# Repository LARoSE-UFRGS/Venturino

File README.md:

# Venturino: an Arduino-Based Open-Hardware platform for educational purposes

About this repo: Schematics, PCB layouts and Software libs.

*This project is intended to be arduino compatible.

LARoSE - UFRGS

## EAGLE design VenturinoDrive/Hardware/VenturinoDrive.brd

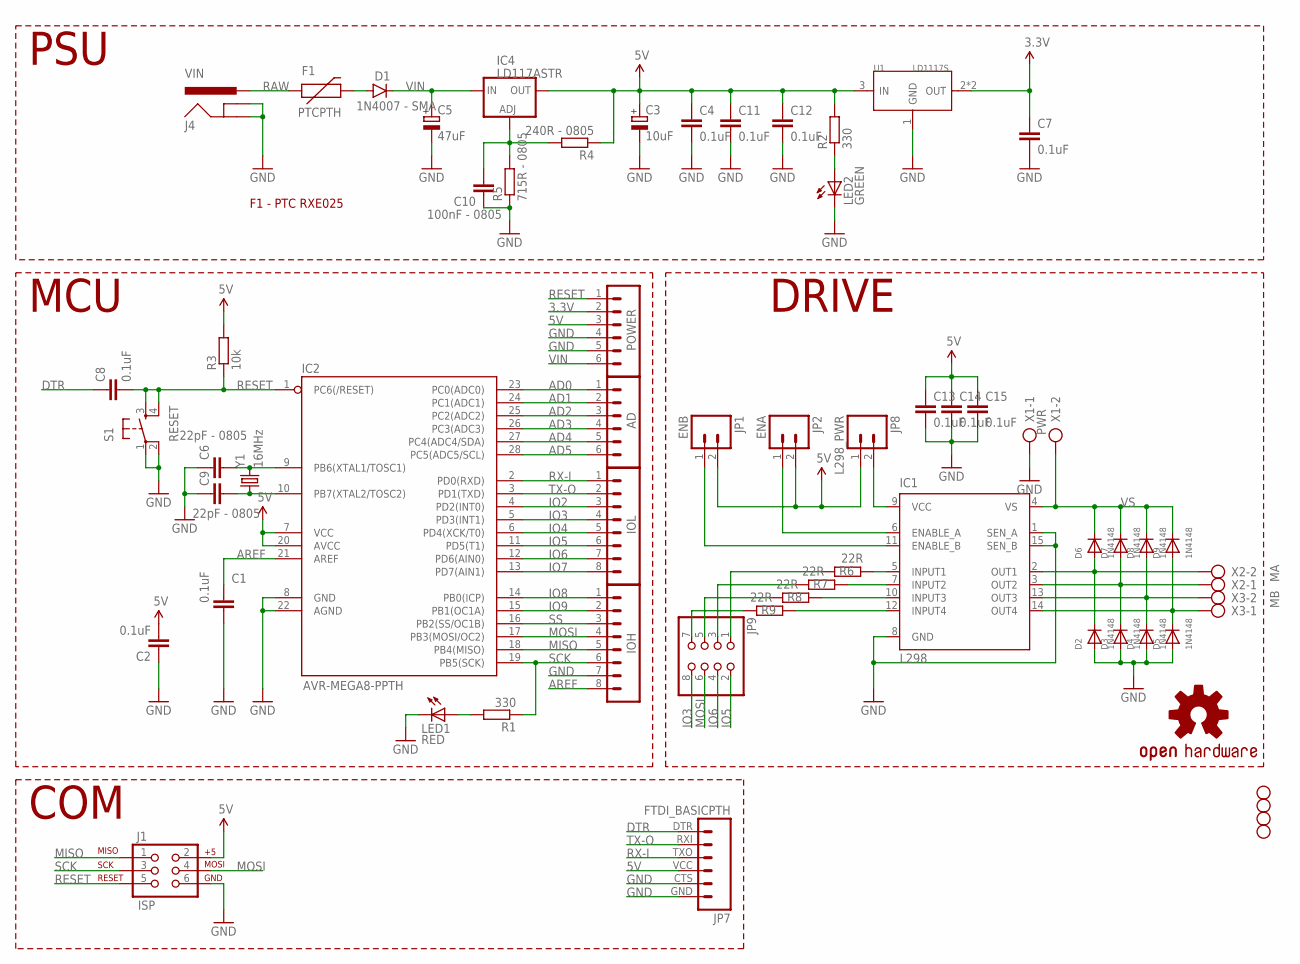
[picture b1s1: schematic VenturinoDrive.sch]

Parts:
AD: M06SIP; 1X06
C1, C2, C4, C7, C8, C11, C12, C13, C14, C15: 0.1uF; C0805
C3: 10uF; PANASONIC_B
C5: 47uF; PANASONIC_B
C6, C9: 22pF - 0805; C0805
C10: 100nF - 0805; C0805
D1: 1N4007 - SMA; SMA-DIODE
D2, D3, D4, D5, D6, D7, D8, D9: 1N4148; SMADIODE
F1: PTCPTH; PTC
IC1: L298; MULTIWATT-15
IC2: AVR-MEGA8-PPTH; DIL28-3
IC4: LD117ASTR; SOT223
IOH: M081X08; 1X08
IOL: M081X08; 1X08
J1: ISP; 2X3
J4: VIN; POWER_JACK_PTH_LOCK
JP1: ENB; 1X02
JP2: ENA; 1X02
JP3, JP4, JP5, JP6: STAND-OFF
JP7: FTDI_BASICPTH; FTDI_BASIC
JP8: L298_PWR; 1X02
JP9: PINHD-2X4; 2X04
LED1: RED; SML0805
LED2: GREEN; SML0805
POWER: M06SIP; 1X06
R1, R2: 330; R0805
R3: 10k; R0805
R4: 240R - 0805; R0805
R5: 715R - 0805; R0805
R6, R7, R8, R9: 22R; R0805
S1: RESET; TACTILE-PTH
U1: LD1117S; SOT-223
U$7: OSHW-LOGOM; OSHW-LOGO-M
X1: PWR; AK500/2
X2: MA; AK500/2
X3: MB; AK500/2
Y1: 16MHz; HC49US

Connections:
3.3V: C7.1, POWER.2, U1.2 (OUT), U1.TER (OUT)
5V: C2.2, C3.+, C4.1, C11.1, C12.1, C13.1, C14.1, C15.1, IC2.7 (VCC), IC2.20 (AVCC), IC4.4 (OUT), J1.2, JP1.2, JP2.2, JP7.VCC (4), JP8.1, POWER.3, R2.2, R3.2, R4.1, U1.3 (IN)
AD0: AD.1, IC2.23 (PC0(ADC0))
AD1: AD.2, IC2.24 (PC1(ADC1))
AD2: AD.3, IC2.25 (PC2(ADC2))
AD3: AD.4, IC2.26 (PC3(ADC3))
AD4: AD.5, IC2.27 (PC4(ADC4/SDA))
AD5: AD.6, IC2.28 (PC5(ADC5/SCL))
AREF: C1.1, IC2.21 (AREF), IOH.8
DTR: C8.1, JP7.DTR (1)
GND: C1.2, C2.1, C3.-, C4.2, C5.-, C6.1, C7.2, C9.1, C10.1, C11.2, C12.2, C13.2, C14.2, C15.2, D2.A, D3.A, D4.A, D5.A, IC1.1 (SEN_A), IC1.8 (GND), IC1.15 (SEN_B), IC2.8 (GND), IC2.22 (AGND), IOH.7, J1.6, J4.GND, J4.GNDBREAK, JP7.CTS (5), JP7.GND (6), LED1.C, LED2.C, POWER.4, POWER.5, R5.1, S1.1, S1.2, U1.1 (GND), X1.1
IO2: IC2.4 (PD2(INT0)), IOL.3
IO3: IC2.5 (PD3(INT1)), IOL.4, JP9.8
IO4: IC2.6 (PD4(XCK/T0)), IOL.5
IO5: IC2.11 (PD5(T1)), IOL.6, JP9.2
IO6: IC2.12 (PD6(AIN0)), IOL.7, JP9.4
IO7: IC2.13 (PD7(AIN1)), IOL.8
IO8: IC2.14 (PB0(ICP)), IOH.1
IO9: IC2.15 (PB1(OC1A)), IOH.2
MISO: IC2.18 (PB4(MISO)), IOH.5, J1.1
MOSI: IC2.17 (PB3(MOSI/OC2)), IOH.4, J1.4, JP9.6
unnamed: LED1.A, R1.2
unnamed: LED2.A, R2.1
unnamed: C6.2, IC2.9 (PB6(XTAL1/TOSC1)), Y1.2
unnamed: C9.2, IC2.10 (PB7(XTAL2/TOSC2)), Y1.1
unnamed: JP9.7, R9.2
unnamed: D1.A, F1.P$2 (2)
unnamed: JP9.5, R8.2
unnamed: C10.2, IC4.1 (ADJ), R4.2, R5.2
unnamed: JP9.3, R7.2
unnamed: IC1.6 (ENABLE_A), JP2.1
unnamed: IC1.11 (ENABLE_B), JP1.1
unnamed: IC1.9 (VCC), JP8.2
unnamed: JP9.1, R6.2
unnamed: D2.C, D6.A, IC1.2 (OUT1), X2.2
unnamed: D3.C, D7.A, IC1.3 (OUT2), X2.1
unnamed: D4.C, D8.A, IC1.13 (OUT3), X3.2
unnamed: D5.C, D9.A, IC1.14 (OUT4), X3.1
unnamed: IC1.5 (INPUT1), R6.1
unnamed: IC1.7 (INPUT2), R7.1
unnamed: IC1.10 (INPUT3), R8.1
unnamed: IC1.12 (INPUT4), R9.1
RAW: F1.P$1 (1), J4.PWR
RESET: C8.2, IC2.1 (PC6(/RESET)), J1.5, POWER.1, R3.1, S1.3, S1.4
RX-I: IC2.2 (PD0(RXD)), IOL.1, JP7.TXO (3)
SCK: IC2.19 (PB5(SCK)), IOH.6, J1.3, R1.1
SS: IC2.16 (PB2(SS/OC1B)), IOH.3
TX-O: IC2.3 (PD1(TXD)), IOL.2, JP7.RXI (2)
VIN: C5.+, D1.C, IC4.3 (IN), POWER.6
VS: D6.C, D7.C, D8.C, D9.C, IC1.4 (VS), X1.2

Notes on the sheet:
PSU
MCU
COM
DRIVE
F1 - PTC RXE025

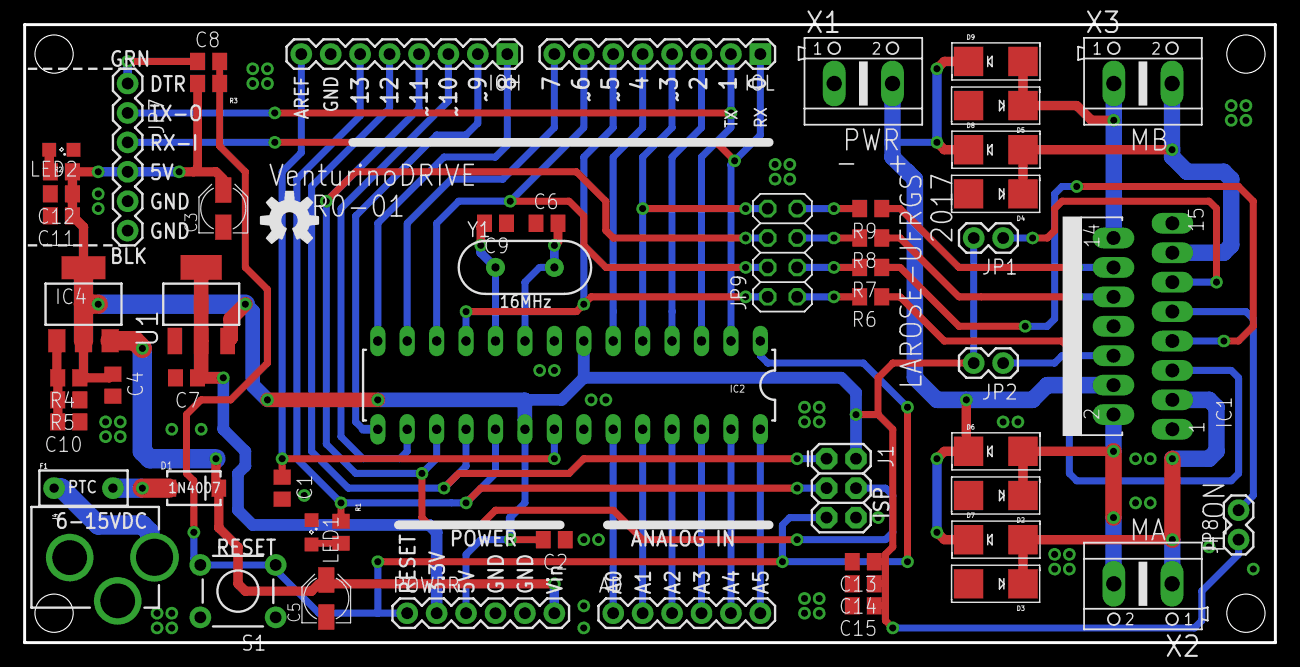
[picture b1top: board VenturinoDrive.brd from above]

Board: 2 copper layers, 108.0 x 53.3 mm, 61 parts (0 on the bottom side), 50 nets.

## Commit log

2017-07-15 Set theme jekyll-theme-dinky
2017-08-04 test
2017-08-04 "updates"

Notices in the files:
parts and their libraries:
SparkFun-DiscreteSemi: Licensing: Creative Commons ShareAlike 4.0 International - https://creativecommons.org/licenses/by-sa/4.0
